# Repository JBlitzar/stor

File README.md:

# stor

A USB2.0 High Speed flash drive with a hotswappable MicroSD backend. 

The specs:

- USB 2.0 Hi-Speed
- STM32H723VGT6 MCU (Cortex-M7, 550 MHz class)
- MicroSDXC backend, up to 2 TB
- ~30–40 MB/s sustained, approximately saturating USB2.0

I made this because I always thought USB flash drives were pretty neat. So much storage! Easy file transfer! Ability to USB-boot! Making my own seemed like the perfect justification. Then, I saw that eMMC prices have in fact been inflated in accordance with the whole 2026 AI RAM shortage thing. You know what is still cheap per GB? microSD. You can absolutely get a respectable amount of storage (64gb, 128gb, 256gb) for just $10-20 if you source smartly. And microSDs have endless customization. They go up to 2TB. There exist industrially-rated ones with super high endurance. And, unlike BGA eMMC, they are hot-swappable.

The STM middleman is also fun because it means I can do all sorts of things, from custom USB descriptors to on-the-fly encryption or compression. The H7 even has crypto primitives, so it would be lightning fast! Implementation of this coming soon after the initial firmware is validated.

## Schematic

## PCB

[Kicanvas](https://kicanvas.org/?repo=https%3A%2F%2Fgithub.com%2FJBlitzar%2Fstor%2Ftree%2Fmain%2FPCB%2Fstor)

F.cu and B.cu:

## Usage

Standard USB to UART flashing configuration. Wiring diagram:

To flash the firmware:

1. `cd firmware`
2. Hold BOOT0, tap reset, release BOOT0
2. Run: `pio run -t upload`
3. Monitor: `pio device monitor`

It also might be possible to flash over USB. I haven't tested it though. Instructions are in [firmware/README.md](firmware/README.md), but in short:

1. `cd firmware`
2. `pio run` (to build)
3. Plug in the board, hold BOOT0, tap reset, release BOOT0
4. `dfu-util -a 0 -s 0x08000000:leave -D .pio/build/stor/firmware.bin`

I'll make this the default `pio run -t upload` behavior after it's been tested and verified.

Only plug in a microsd card after a successful first flash!

## CAD

Assembly STEP is at [cad/stor_assembly.step](cad/stor_assembly.step)

Case STEP is at [cad/stor_case.step](cad/stor_case.step)

Case is attached to the PCB through the circular pegs that go into the holes in the PCB

Onshape link: https://cad.onshape.com/documents/a7e5e47cc0cfc056916b5738/w/17c4e94553a6fc2d4495a917/e/2d8b03d1ea07a2cbf9c4bec4?renderMode=0&uiState=6a7fdac0fa02538896f51f27

## Credits

[TinyUSB](https://github.com/hathach/tinyusb) for the USB stack! LICENSE file is included in [firmware/lib/tinyusb](firmware/lib/tinyusb)

## BOM

|Item                |Link                                                 |Cost |Notes                                                                                                                                                                                                                    |
|--------------------|-----------------------------------------------------|-----|-------------------------------------------------------------------------------------------------------------------------------------------------------------------------------------------------------------------------|
|CP2102 for flashing |http://waveshare.com/cp2102-usb-uart-board-type-a.htm|0    |Cost is zero because I'm flashing via FPGA. For others looking to reproduce, this is the simplest thing you can buy                                                                                                      |
|SD card             |https://www.lcsc.com/product-detail/C42416580.html   |0    |I'll be paying out of pocket or self-sourcing. Feel free to gnab whatever listing you want, this is a 128gb listing for which I have no idea if it'll be reputable. Your safest bet is a sandisk off of amazon or digikey|
|PCB                 |N/A                                                  |7.1  |green pcb; other colors cost $5 more                                                                                                                                                                                     |
|PCBA                |N/A                                                  |67.97|2x PCBA is the MOQ                                                                                                                                                                                                       |
|JLC shipping + taxes|N/A                                                  |3.3  |Shipping special offer; may cost up to $8, but at the same time I have some coupons. So the total will work out about the same                                                                                           |
|Total               |N/A                                                  |78.37|                                                                                                                                                                                                                         |
### Fabrication BOM

You'll find the rest of the fabrication outputs at [PCB/stor/production_real](PCB/stor/production_real)

|Designator          |Footprint                                            |Quantity|Value                                                                                                                                                                                                                    |LCSC Part #|
|--------------------|-----------------------------------------------------|--------|-------------------------------------------------------------------------------------------------------------------------------------------------------------------------------------------------------------------------|-----------|
|C1, C16, C2         |C0402                                                |3       |2.2uF                                                                                                                                                                                                                    |C12530     |
|C10, C15, C18, C19, C21, C23, C26, C27, C3, C4, C5, C6, C7, C8, C9|C0402                                                |15      |100nF                                                                                                                                                                                                                    |C1525      |
|C11, C12, C13, C14, C24, C25|C0402                                                |6       |18pF                                                                                                                                                                                                                     |C1549      |
|C17                 |C0603                                                |1       |22uF                                                                                                                                                                                                                     |C59461     |
|C20, C22, C29       |C0402                                                |3       |4.7uF                                                                                                                                                                                                                    |C23733     |
|CARD1               |TF-SMD_TF-01A                                        |1       |TF-01A                                                                                                                                                                                                                   |C91145     |
|D1                  |SOT-23-6_L2.9-W1.6-P0.95-LS2.8-BL                    |1       |USBLC6-2SC6                                                                                                                                                                                                              |C7519      |
|J1                  |PinSocket_1x05_P2.54mm_Vertical                      |1       |Conn_01x05_Socket                                                                                                                                                                                                        |           |
|J2                  |PinSocket_1x04_P2.54mm_Vertical                      |1       |Conn_01x04_Socket                                                                                                                                                                                                        |           |
|L1                  |IND-SMD_L3.2-W2.5_CKST322512-2.2UH                   |1       |10uH                                                                                                                                                                                                                     |C39846661  |
|LED1                |LED-SMD_L1.6-W0.8-R-RD                               |1       |KT-0603R                                                                                                                                                                                                                 |C2286      |
|LED2                |LED0603-R-RD_WHITE                                   |1       |0603White light_C2290                                                                                                                                                                                                    |C2290      |
|R1, R10, R11, R7, R8, R9|R0402                                                |6       |10k                                                                                                                                                                                                                      |C25744     |
|R12                 |R0402                                                |1       |220Ω                                                                                                                                                                                                                     |C25091     |
|R3                  |R0402                                                |1       |1kΩ                                                                                                                                                                                                                      |C11702     |
|R4                  |R0402                                                |1       |100k                                                                                                                                                                                                                     |C25741     |
|R5                  |R0402                                                |1       |12k                                                                                                                                                                                                                      |C25752     |
|R6                  |R0402                                                |1       |1 MΩ                                                                                                                                                                                                                     |C26083     |
|SW1, SW2            |SW-SMD_4P-L4.5-W4.5-P3.00-LS6.8                      |2       |TS1603-TZ38HBM                                                                                                                                                                                                           |C36938886  |
|U1                  |LQFP-100_L14.0-W14.0-P0.50-LS16.0-BL                 |1       |STM32H723VGT6                                                                                                                                                                                                            |C730142    |
|U3                  |QFN-32_L5.0-W5.0-P0.50-BL-EP3.4                      |1       |USB3300-EZK-TR                                                                                                                                                                                                           |C108383    |
|U4                  |WSON-10_L3.0-W2.0-P0.50-BL-EP                        |1       |TPS62177DQCR                                                                                                                                                                                                             |C91241     |
|USB1                |USB-SMD_KH-USB-AM-4P-CB                              |1       |U-USBAR04P-M001                                                                                                                                                                                                          |C386752    |
|X1                  |CRYSTAL-SMD_4P-L3.2-W2.5-BL                          |1       |25mhz                                                                                                                                                                                                                    |C9006      |
|X2                  |OSC-SMD_L3.2-W1.5                                    |1       |32.768k                                                                                                                                                                                                                  |C97606     |
|X3                  |CRYSTAL-SMD_4P-L3.2-W2.5-BL                          |1       |24mhz                                                                                                                                                                                                                    |C7420736   |

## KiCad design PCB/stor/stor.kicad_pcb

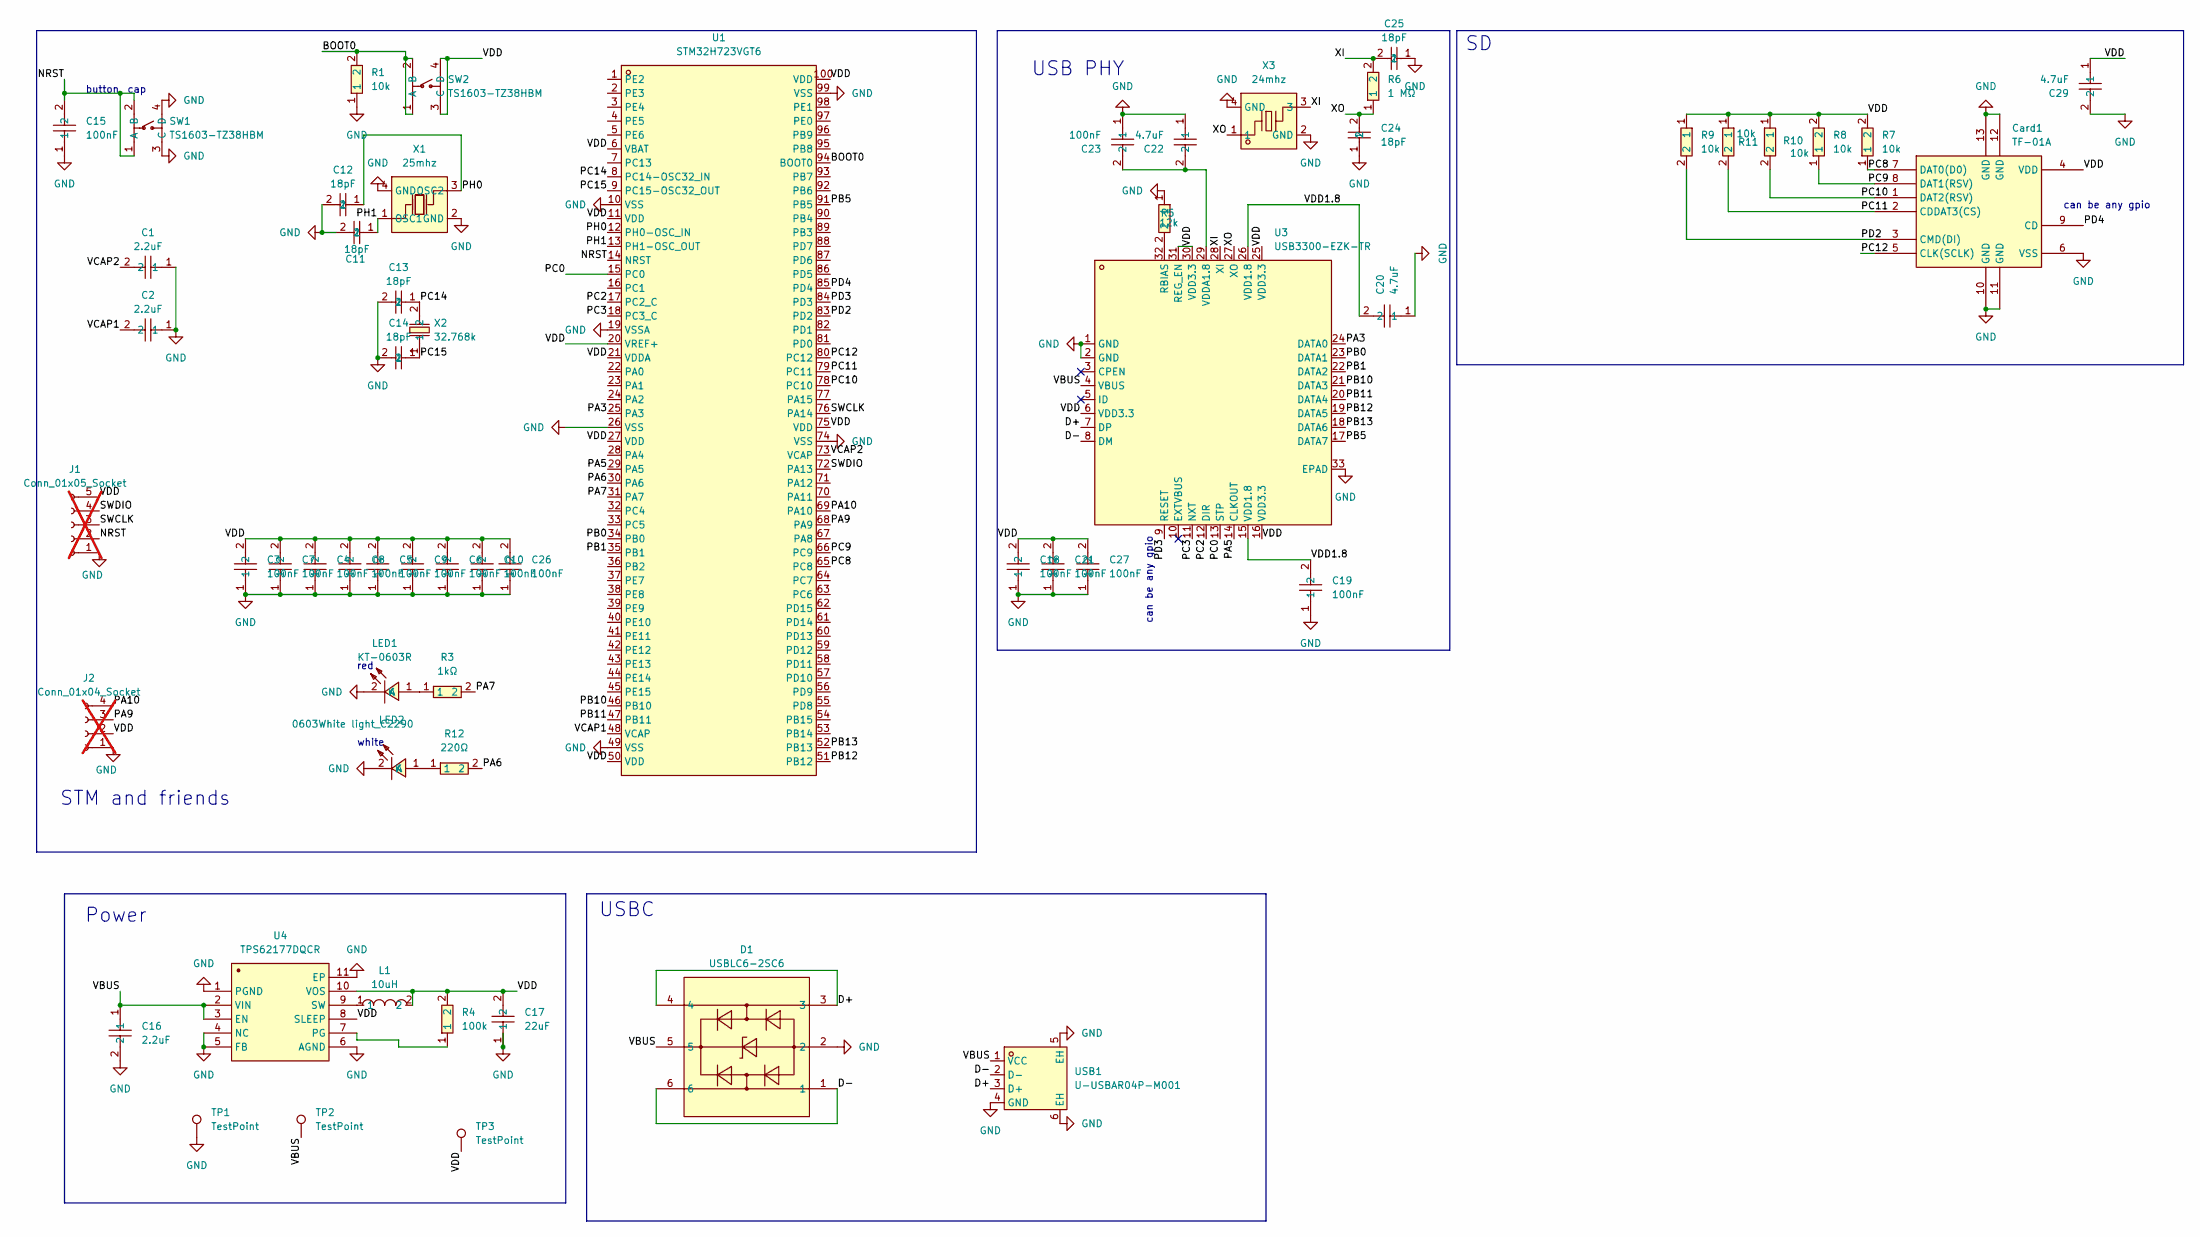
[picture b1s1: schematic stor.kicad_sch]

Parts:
C1, C2, C16: 2.2uF; C0402; MPN CL05A225MQ5NSNC; LCSC Part C12530
C3, C4, C5, C6, C7, C8, C9, C10, C15, C18, C19, C21, C23, C26, C27: 100nF; C0402; MPN CL05B104KO5NNNC; LCSC Part C1525
C11, C12, C13, C14, C24, C25: 18pF; C0402; MPN 0402CG180J500NT; LCSC Part C1549
C17: 22uF; C0603; MPN CL10A226MQ8NRNC; LCSC Part C59461
C20, C22, C29: 4.7uF; C0402; MPN CL05A475MP5NRNC; LCSC Part C23733
Card1: TF-01A; TF-SMD_TF-01A; MPN TF-01A; LCSC Part C91145
D1: USBLC6-2SC6; SOT-23-6_L2.9-W1.6-P0.95-LS2.8-BL; MPN USBLC6-2SC6; LCSC Part C7519
J1: Conn_01x05_Socket; PinSocket_1x05_P2.54mm_Vertical; not fitted
J2: Conn_01x04_Socket; PinSocket_1x04_P2.54mm_Vertical; not fitted
L1: 10uH; IND-SMD_L3.2-W2.5_CKST322512-2.2UH; MPN XRTC322512S100MBCA; LCSC Part C39846661
LED1: KT-0603R; LED-SMD_L1.6-W0.8-R-RD; MPN KT-0603R; LCSC Part C2286
LED2: 0603White light_C2290; LED0603-R-RD_WHITE; MPN KT-0603W; LCSC Part C2290
R1, R7, R8, R9, R10, R11: 10k; R0402; MPN 0402WGF1002TCE; LCSC Part C25744
R3: 1kΩ; R0402; MPN 0402WGF1001TCE; LCSC Part C11702
R4: 100k; R0402; MPN 0402WGF1003TCE; LCSC Part C25741
R5: 12k; R0402; MPN 0402WGF1202TCE; LCSC Part C25752
R6: 1 MΩ; R0402; MPN 0402WGF1004TCE; LCSC Part C26083
R12: 220Ω; R0402; MPN 0402WGF2200TCE; LCSC Part C25091
SW1, SW2: TS1603-TZ38HBM; SW-SMD_4P-L4.5-W4.5-P3.00-LS6.8; MPN TS1603-TZ38HBM; LCSC Part C36938886
TP1, TP2, TP3: TestPoint; TestPoint_Pad_2.0x2.0mm
U1: STM32H723VGT6; LQFP-100_L14.0-W14.0-P0.50-LS16.0-BL; MPN STM32H723VGT6; LCSC Part C730142
U3: USB3300-EZK-TR; QFN-32_L5.0-W5.0-P0.50-BL-EP3.4; MPN USB3300-EZK-TR; LCSC Part C108383
U4: TPS62177DQCR; WSON-10_L3.0-W2.0-P0.50-BL-EP; MPN TPS62177DQCR; LCSC Part C91241
USB1: U-USBAR04P-M001; USB-SMD_KH-USB-AM-4P-CB; MPN U-USBAR04P-M003; LCSC Part C386752
X1: 25mhz; CRYSTAL-SMD_4P-L3.2-W2.5-BL; MPN X322525MOB4SI; LCSC Part C9006
X2: 32.768k; OSC-SMD_L3.2-W1.5; MPN SC-32S32.768kHz20PPM12.5pF; LCSC Part C97606
X3: 24mhz; CRYSTAL-SMD_4P-L3.2-W2.5-BL; MPN SX32Y024000BC1T001; LCSC Part C7420736

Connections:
/BOOT0: R1.2, SW2.1 (A), SW2.2 (B), U1.94 (BOOT0)
/D+: D1.3, D1.4, U3.7 (DP), USB1.3 (D+)
/D-: D1.1, D1.6, U3.8 (DM), USB1.2 (D-)
/NRST: C15.2, J1.2, SW1.1 (A), SW1.2 (B), U1.14 (NRST)
/PA3: U1.25 (PA3), U3.24 (DATA0)
/PA5: U1.29 (PA5), U3.14 (CLKOUT)
/PA6: R12.2, U1.30 (PA6)
/PA7: R3.2, U1.31 (PA7)
/PA9: J2.3, U1.68 (PA9)
/PA10: J2.4, U1.69 (PA10)
/PB0: U1.34 (PB0), U3.23 (DATA1)
/PB1: U1.35 (PB1), U3.22 (DATA2)
/PB5: U1.91 (PB5), U3.17 (DATA7)
/PB10: U1.46 (PB10), U3.21 (DATA3)
/PB11: U1.47 (PB11), U3.20 (DATA4)
/PB12: U1.51 (PB12), U3.19 (DATA5)
/PB13: U1.52 (PB13), U3.18 (DATA6)
/PC0: U1.15 (PC0), U3.13 (STP)
/PC2: U1.17 (PC2_C), U3.12 (DIR)
/PC3: U1.18 (PC3_C), U3.11 (NXT)
/PC8: Card1.7 (DAT0(D0)), R7.1, U1.65 (PC8)
/PC9: Card1.8 (DAT1(RSV)), R8.1, U1.66 (PC9)
/PC10: Card1.1 (DAT2(RSV)), R10.2, U1.78 (PC10)
/PC11: Card1.2 (CDDAT3(CS)), R11.2, U1.79 (PC11)
/PC12: Card1.5 (CLK(SCLK)), U1.80 (PC12)
/PC14: C13.1, U1.8 (PC14-OSC32_IN), X2.2
/PC15: C14.1, U1.9 (PC15-OSC32_OUT), X2.1
/PD2: Card1.3 (CMD(DI)), R9.2, U1.83 (PD2)
/PD3: U1.84 (PD3), U3.9 (RESET)
/PD4: Card1.9 (CD), U1.85 (PD4)
/PH0: C12.1, U1.12 (PH0-OSC_IN), X1.3 (OSC2)
/PH1: C11.1, U1.13 (PH1-OSC_OUT), X1.1 (OSC1)
/SWCLK: J1.3, U1.76 (PA14)
/SWDIO: J1.4, U1.72 (PA13)
/VBUS: C16.1, D1.5, TP2.1 (1_1), U3.4 (VBUS), U4.2 (VIN), U4.3 (EN), USB1.1 (VCC)
/VCAP1: C2.2, U1.48 (VCAP)
/VCAP2: C1.2, U1.73 (VCAP)
/VDD: C3.2, C4.2, C5.2, C6.2, C7.2, C8.2, C9.2, C10.2, C17.2, C18.2, C21.2, C26.2, C27.2, C29.1, Card1.4 (VDD), J1.5, J2.2, L1.2, R4.2, R7.2, R8.2, R9.1, R10.1, R11.1, SW2.3 (C), SW2.4 (D), TP3.1 (1_1), U1.6 (VBAT), U1.11 (VDD), U1.20 (VREF+), U1.21 (VDDA), U1.27 (VDD), U1.50 (VDD), U1.75 (VDD), U1.100 (VDD), U3.6 (VDD3.3), U3.16 (VDD3.3), U3.25 (VDD3.3), U3.30 (VDD3.3), U3.31 (REG_EN), U4.8 (SLEEP), U4.10 (VOS)
/VDD1.8: C19.2, C20.2, U3.15 (VDD1.8), U3.26 (VDD1.8)
/XI: C25.2, R6.2, U3.28 (XI), X3.3
/XO: C24.2, R6.1, U3.27 (XO), X3.1
GND: C1.1, C2.1, C3.1, C4.1, C5.1, C6.1, C7.1, C8.1, C9.1, C10.1, C11.2, C12.2, C13.2, C14.2, C15.1, C16.2, C17.1, C18.1, C19.1, C20.1, C21.1, C22.1, C23.1, C24.1, C25.1, C26.1, C27.1, C29.2, Card1.6 (VSS), Card1.10 (GND), Card1.11 (GND), Card1.12 (GND), Card1.13 (GND), D1.2, J1.1, J2.1, LED1.2 (K), LED2.2 (K), R1.1, R5.1, SW1.3 (C), SW1.4 (D), TP1.1 (1_1), U1.10 (VSS), U1.19 (VSSA), U1.26 (VSS), U1.49 (VSS), U1.74 (VSS), U1.99 (VSS), U3.1 (GND), U3.2 (GND), U3.33 (EPAD), U4.1 (PGND), U4.4 (NC), U4.5 (FB), U4.6 (AGND), U4.11 (EP), USB1.4 (GND), USB1.5 (EH), USB1.6 (EH), X1.2 (GND), X1.4 (GND), X3.2 (GND), X3.4 (GND)
unnamed: LED1.1 (A), R3.1
unnamed: LED2.1 (A), R12.1
unnamed: R5.2, U3.32 (RBIAS)
unnamed: C22.2, C23.2, U3.29 (VDDA1.8)
unnamed: R4.1, U4.7 (PG)
unnamed: L1.1, U4.9 (SW)

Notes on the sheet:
can be any gpio
USBC
white
red
STM and friends
can be any gpio
USB PHY
Power
button, cap

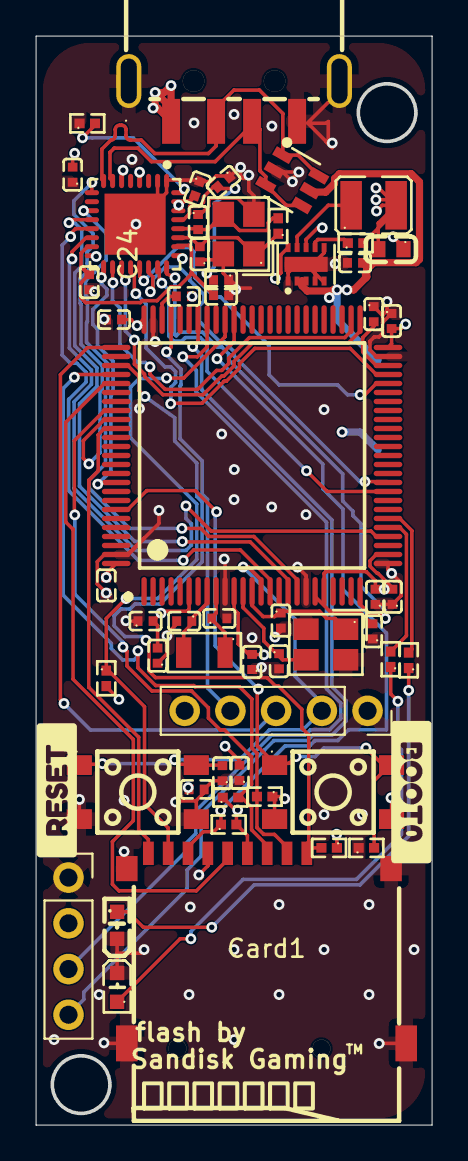
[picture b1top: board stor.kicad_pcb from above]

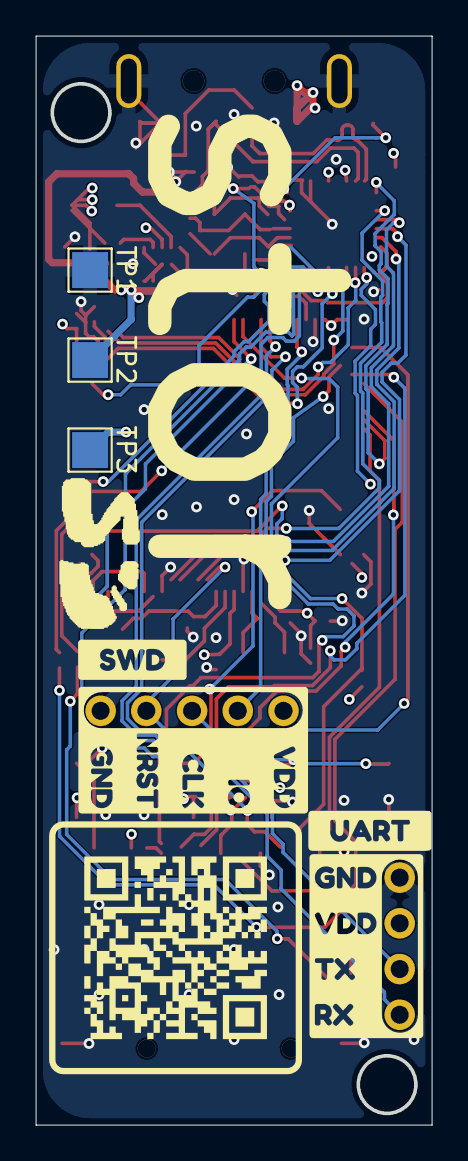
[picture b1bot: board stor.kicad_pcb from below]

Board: 4 copper layers, 22.0 x 60.5 mm, 65 parts (8 on the bottom side), 48 nets.

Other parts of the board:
kobee-studio-6A81F80C: Kobee Studio; kobee-studio-6A81F4CE
kobee-studio-6A8143AA: Kobee Studio; kobee-studio-6A8143AA
kobee-studio-6A8143BF: Kobee Studio; kobee-studio-6A8143BF
kobee-studio-6A8144FF: Kobee Studio; kobee-studio-6A8144FF
kobee-studio-6A81454B: Kobee Studio; kobee-studio-6A81454B
kobee-studio-6A814325: Kobee Studio; kobee-studio-6A814325
kobee-studio-6A814354: Kobee Studio; kobee-studio-6A814354

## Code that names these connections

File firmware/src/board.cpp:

#include "board.hpp"

#include "stm32h7xx_hal.h"

namespace {


GPIO_TypeDef* const kLedActivityPort = GPIOA;
constexpr uint16_t kLedActivityPin = GPIO_PIN_6;
GPIO_TypeDef* const kLedErrorPort = GPIOA;
constexpr uint16_t kLedErrorPin = GPIO_PIN_7;

constexpr uint16_t kPhyResetPin = GPIO_PIN_3;   // PD3, active high
constexpr uint16_t kCardDetectPin = GPIO_PIN_4; // PD4
constexpr uint16_t kUlpiClockPin = GPIO_PIN_5;  // PA5

struct PinCfg {
  GPIO_TypeDef* port;
  uint16_t pin;
  uint32_t mode;
  uint32_t pull;
  uint32_t alternate;
};

const PinCfg kPins[] = {
    // ULPI: CK, D0-D7, STP, DIR, NXT
    {GPIOA, GPIO_PIN_5, GPIO_MODE_AF_PP, GPIO_NOPULL, GPIO_AF10_OTG1_HS},
    {GPIOA, GPIO_PIN_3, GPIO_MODE_AF_PP, GPIO_NOPULL, GPIO_AF10_OTG1_HS},
    {GPIOB, GPIO_PIN_0, GPIO_MODE_AF_PP, GPIO_NOPULL, GPIO_AF10_OTG1_HS},
    {GPIOB, GPIO_PIN_1, GPIO_MODE_AF_PP, GPIO_NOPULL, GPIO_AF10_OTG1_HS},
    {GPIOB, GPIO_PIN_10, GPIO_MODE_AF_PP, GPIO_NOPULL, GPIO_AF10_OTG1_HS},
    {GPIOB, GPIO_PIN_11, GPIO_MODE_AF_PP, GPIO_NOPULL, GPIO_AF10_OTG1_HS},
    {GPIOB, GPIO_PIN_12, GPIO_MODE_AF_PP, GPIO_NOPULL, GPIO_AF10_OTG1_HS},
    {GPIOB, GPIO_PIN_13, GPIO_MODE_AF_PP, GPIO_NOPULL, GPIO_AF10_OTG1_HS},
    {GPIOB, GPIO_PIN_5, GPIO_MODE_AF_PP, GPIO_NOPULL, GPIO_AF10_OTG1_HS},
    {GPIOC, GPIO_PIN_0, GPIO_MODE_AF_PP, GPIO_NOPULL, GPIO_AF10_OTG1_HS},
    {GPIOC, GPIO_PIN_2, GPIO_MODE_AF_PP, GPIO_NOPULL, GPIO_AF10_OTG1_HS},
    {GPIOC, GPIO_PIN_3, GPIO_MODE_AF_PP, GPIO_NOPULL, GPIO_AF10_OTG1_HS},
    // SDMMC1: D0-D3, CK, CMD
    {GPIOC, GPIO_PIN_8, GPIO_MODE_AF_PP, GPIO_NOPULL, GPIO_AF12_SDMMC1},
    {GPIOC, GPIO_PIN_9, GPIO_MODE_AF_PP, GPIO_NOPULL, GPIO_AF12_SDMMC1},
    {GPIOC, GPIO_PIN_10, GPIO_MODE_AF_PP, GPIO_NOPULL, GPIO_AF12_SDMMC1},
    {GPIOC, GPIO_PIN_11, GPIO_MODE_AF_PP, GPIO_NOPULL, GPIO_AF12_SDMMC1},
    {GPIOC, GPIO_PIN_12, GPIO_MODE_AF_PP, GPIO_NOPULL, GPIO_AF12_SDMMC1},
    {GPIOD, GPIO_PIN_2, GPIO_MODE_AF_PP, GPIO_NOPULL, GPIO_AF12_SDMMC1},
    // USART1 console
    {GPIOA, GPIO_PIN_9, GPIO_MODE_AF_PP, GPIO_NOPULL, GPIO_AF7_USART1},
    {GPIOA, GPIO_PIN_10, GPIO_MODE_AF_PP, GPIO_NOPULL, GPIO_AF7_USART1},
    // PHY reset, driven low (released) once configured
    {GPIOD, kPhyResetPin, GPIO_MODE_OUTPUT_PP, GPIO_NOPULL, 0},
    // Card detect
    {GPIOD, kCardDetectPin, GPIO_MODE_INPUT, GPIO_PULLUP, 0},
    // LEDs: PA6 white (activity), PA7 red (error)
    {GPIOA, GPIO_PIN_6, GPIO_MODE_OUTPUT_PP, GPIO_NOPULL, 0},
    {GPIOA, GPIO_PIN_7, GPIO_MODE_OUTPUT_PP, GPIO_NOPULL, 0},
};

void apply(const PinCfg& cfg) {
  GPIO_InitTypeDef init{};
  init.Pin = cfg.pin;
  init.Mode = cfg.mode;
  init.Pull = cfg.pull;
  init.Speed = GPIO_SPEED_FREQ_VERY_HIGH;
  init.Alternate = cfg.alternate;
  HAL_GPIO_Init(cfg.port, &init);
}

}

namespace board {

void init() {
  __HAL_RCC_GPIOA_CLK_ENABLE();
  __HAL_RCC_GPIOB_CLK_ENABLE();
  __HAL_RCC_GPIOC_CLK_ENABLE();
  __HAL_RCC_GPIOD_CLK_ENABLE();
  __HAL_RCC_SYSCFG_CLK_ENABLE();
  __HAL_RCC_USART1_CLK_ENABLE();

  HAL_SYSCFG_AnalogSwitchConfig(SYSCFG_SWITCH_PC2, SYSCFG_SWITCH_PC2_CLOSE);
  HAL_SYSCFG_AnalogSwitchConfig(SYSCFG_SWITCH_PC3, SYSCFG_SWITCH_PC3_CLOSE);

  for (const PinCfg& cfg : kPins) {
    apply(cfg);
  }
}

void reset_phy() {
  HAL_GPIO_WritePin(GPIOD, kPhyResetPin, GPIO_PIN_SET);
  HAL_Delay(1);
  HAL_GPIO_WritePin(GPIOD, kPhyResetPin, GPIO_PIN_RESET);
  HAL_Delay(10);
}

bool phy_clock_alive() {
  GPIO_InitTypeDef probe{};
  probe.Pin = kUlpiClockPin;
  probe.Mode = GPIO_MODE_INPUT;
  probe.Pull = GPIO_NOPULL;
  probe.Speed = GPIO_SPEED_FREQ_VERY_HIGH;
  HAL_GPIO_Init(GPIOA, &probe);

  bool saw_high = false;
  bool saw_low = false;
  for (uint32_t i = 0; i < 100000 && !(saw_high && saw_low); ++i) {
    if (HAL_GPIO_ReadPin(GPIOA, kUlpiClockPin) == GPIO_PIN_SET) {
      saw_high = true;
    } else {
      saw_low = true;
    }
  }

  apply(kPins[0]);
  return saw_high && saw_low;
}

void enable_usb_clocks() {
  __HAL_RCC_USB1_OTG_HS_CLK_ENABLE();
  __HAL_RCC_USB1_OTG_HS_ULPI_CLK_ENABLE();
}

bool card_present() {
  const bool low = HAL_GPIO_ReadPin(GPIOD, kCardDetectPin) == GPIO_PIN_RESET;
  return kCardDetectActiveLow ? low : !low;
}

void led(Led which, bool on) {
  GPIO_TypeDef* port = (which == Led::Activity) ? kLedActivityPort : kLedErrorPort;
  const uint16_t pin = (which == Led::Activity) ? kLedActivityPin : kLedErrorPin;
  HAL_GPIO_WritePin(port, pin, on ? GPIO_PIN_SET : GPIO_PIN_RESET);
}

}
